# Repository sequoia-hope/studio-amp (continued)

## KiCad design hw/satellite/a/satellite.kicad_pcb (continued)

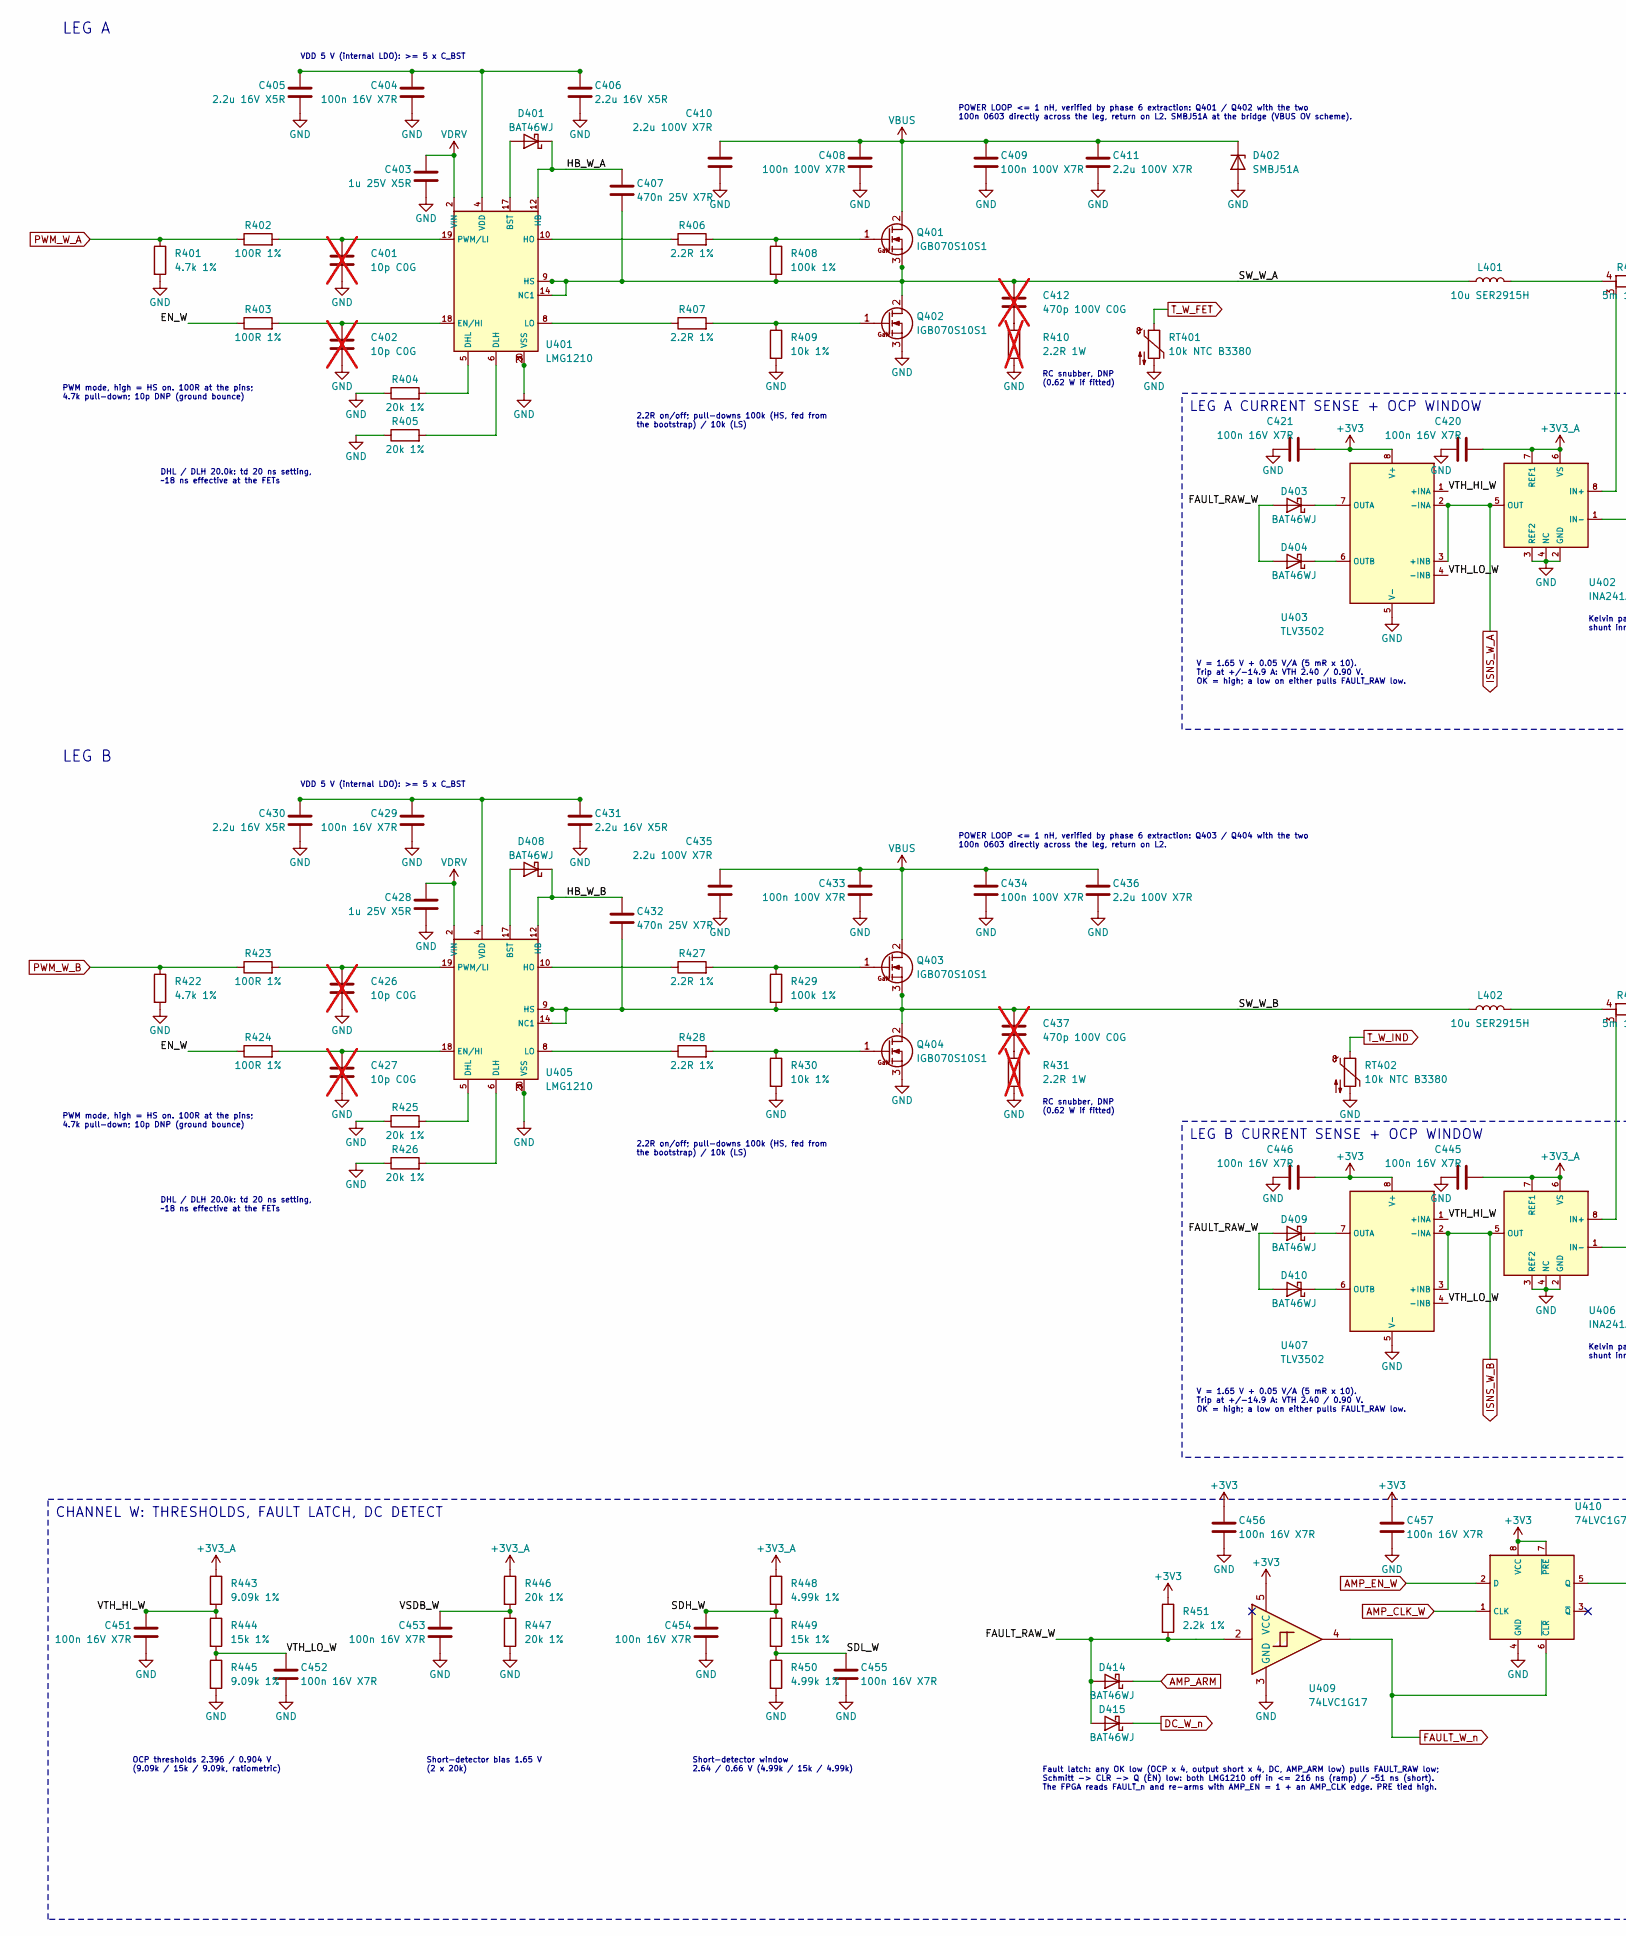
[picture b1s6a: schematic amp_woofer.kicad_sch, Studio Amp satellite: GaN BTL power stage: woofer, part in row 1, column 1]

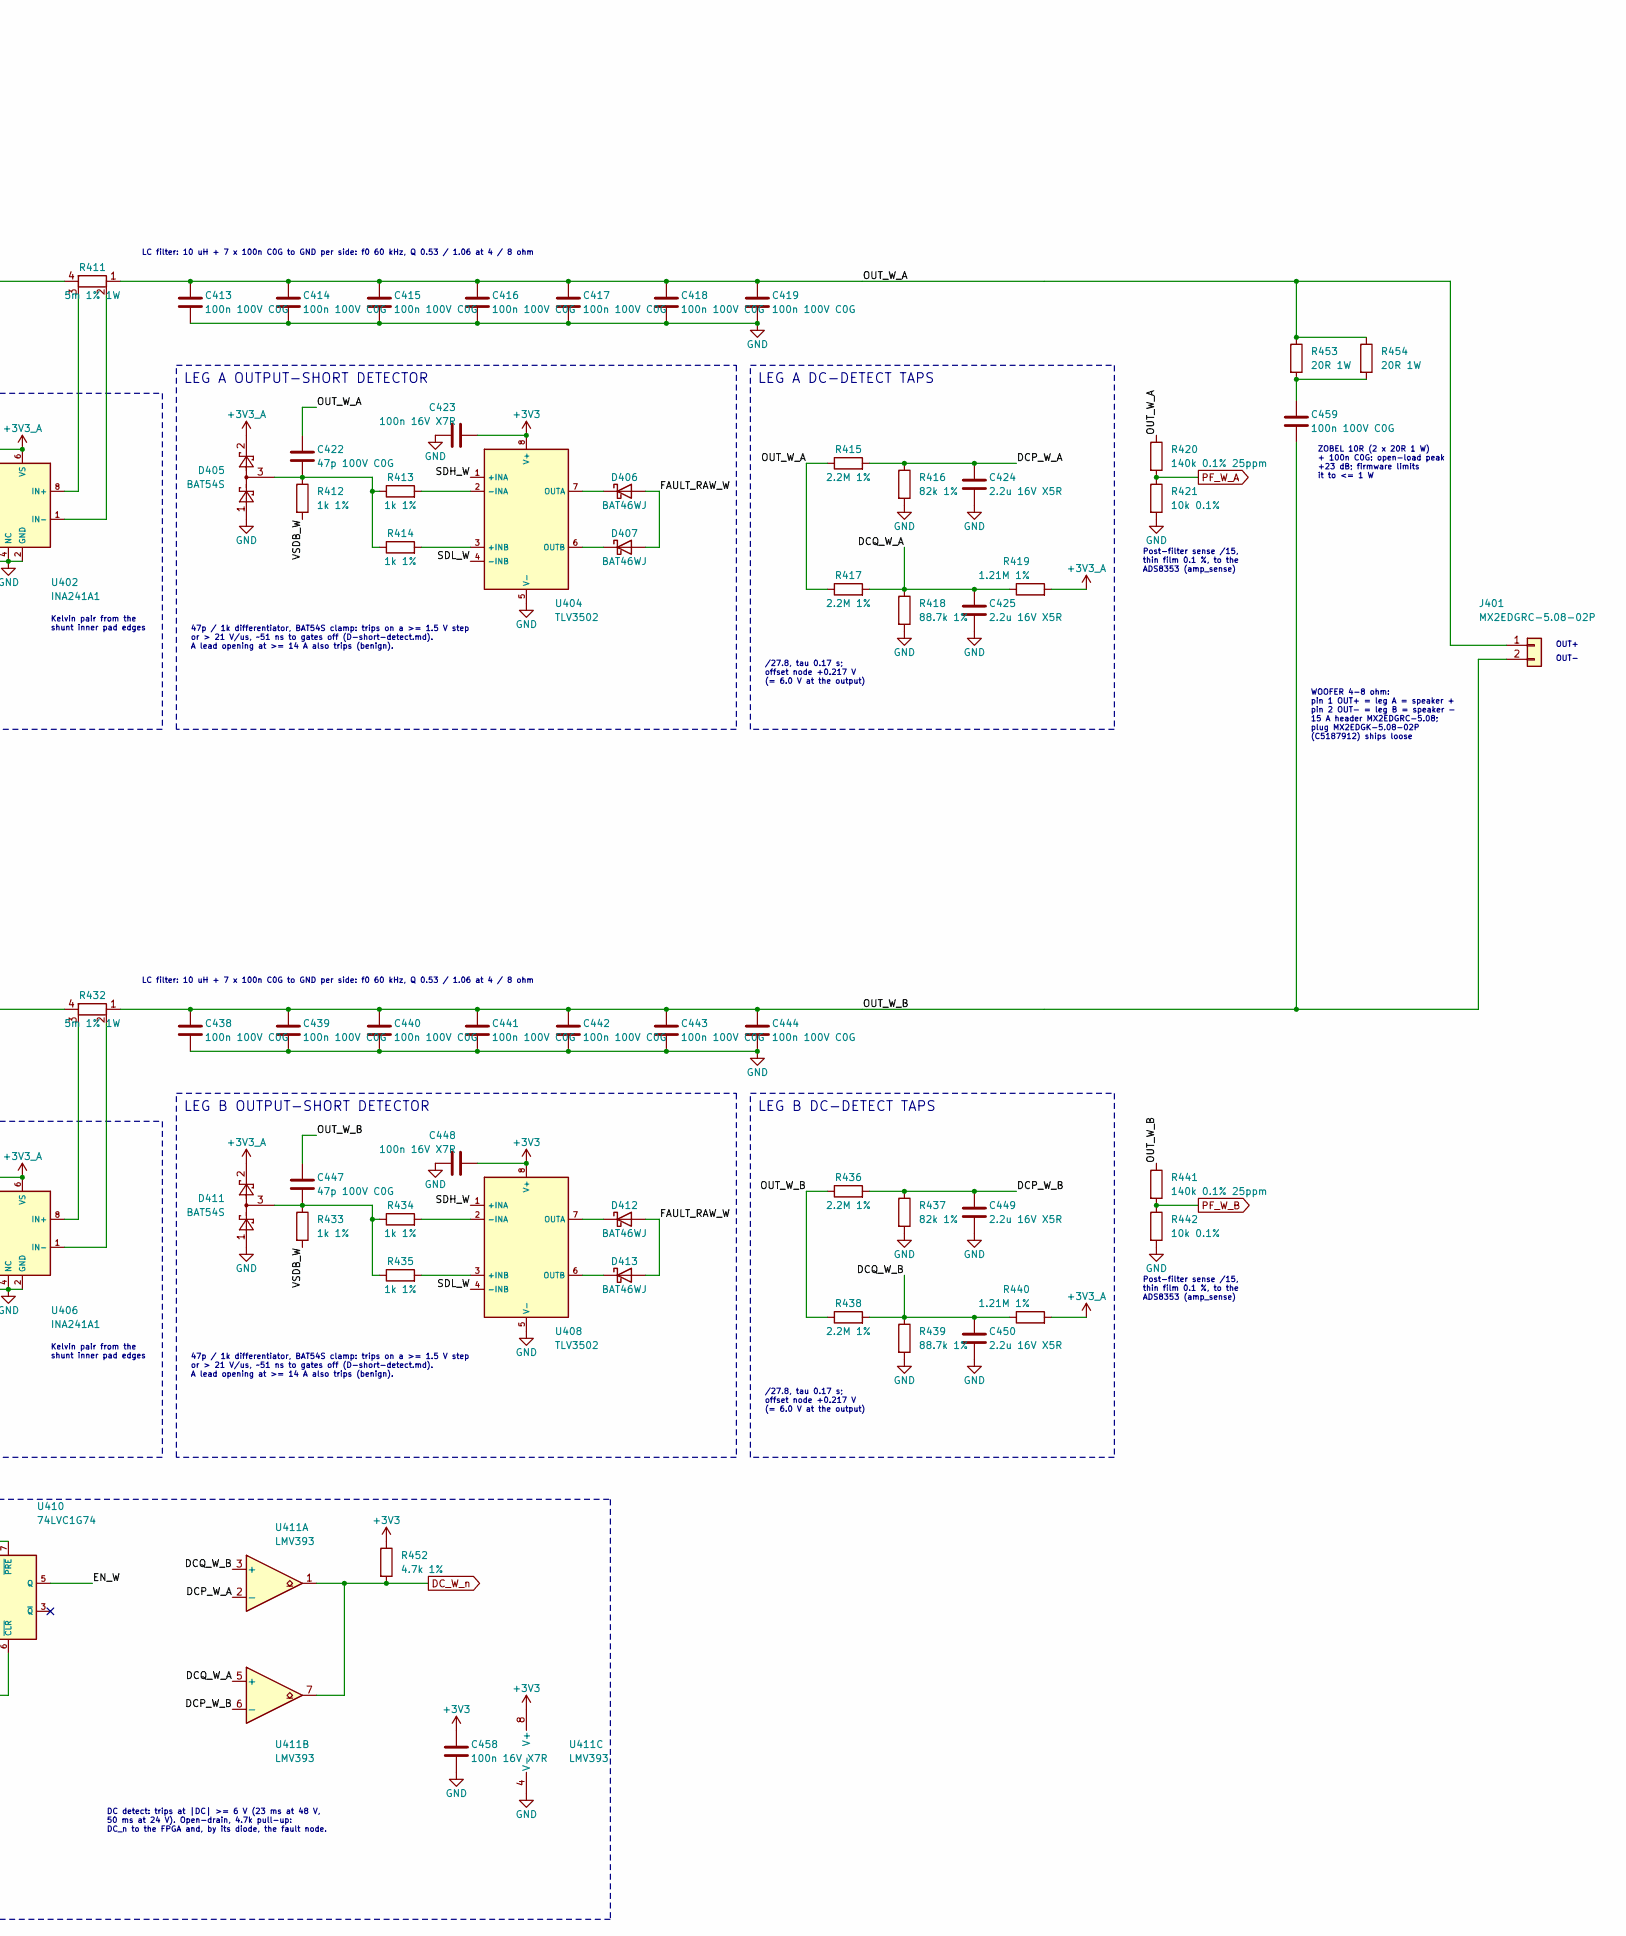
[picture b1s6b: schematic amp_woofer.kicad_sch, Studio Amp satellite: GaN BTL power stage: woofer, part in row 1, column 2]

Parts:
C401, C402, C426, C427: 10p C0G; C_0402_1005Metric; MPN 0402N100J500CT; LCSC C301961; not fitted
C403, C428: 1u 25V X5R; C_0603_1608Metric; MPN CL10A105KA8NNNC; LCSC C5673
C404, C420, C421, C423, C429, C445, C446, C448, C451, C452, C453, C454, C455, C456, C457, C458: 100n 16V X7R; C_0402_1005Metric; MPN CC0402KRX7R7BB104; LCSC C60474
C405, C406, C424, C425, C430, C431, C449, C450: 2.2u 16V X5R; C_0603_1608Metric; MPN CL10A225KO8NNNC; LCSC C23630
C407, C432: 470n 25V X7R; C_0603_1608Metric; MPN CL10B474KA8NNNC; LCSC C1623
C408, C409, C433, C434: 100n 100V X7R; C_0603_1608Metric; MPN HMK107B7104KAHT; LCSC C268011
C410, C411, C435, C436: 2.2u 100V X7R; C_1210_3225Metric; MPN HMK325B7225KN-T; LCSC C92775
C412, C437: 470p 100V C0G; C_0603_1608Metric; MPN CC0603JRNPO0BN471; LCSC C326973; not fitted
C413, C414, C415, C416, C417, C418, C419, C438, C439, C440, C441, C442, C443, C444, C459: 100n 100V C0G; C_1206_3216Metric; MPN GRM31C5C2A104JA01L; LCSC C405303
C422, C447: 47p 100V C0G; C_0603_1608Metric; MPN CC0603JRNPO0BN470; LCSC C327115
D401, D403, D404, D406, D407, D408, D409, D410, D412, D413, D414, D415: BAT46WJ; D_SOD-323F; MPN BAT46WJ,115; LCSC C114696
D402: SMBJ51A; D_SMB; MPN SMBJ51A; LCSC C1973217
D405, D411: BAT54S; SOT-23; MPN BAT54S,215; LCSC C47546
J401: MX2EDGRC-5.08-02P; MAX_MX2EDGRC-5.08-02P_1x02_P5.08mm_Horizontal; MPN MX2EDGRC-5.08-02P-GN01-Cu-A; LCSC C5188019
L401, L402: 10u SER2915H; Coilcraft_SER2915H; MPN SER2915H-103KL; LCSC C19276042
Q401, Q402, Q403, Q404: IGB070S10S1; IGB070S10S1_PG-TSON-4; MPN IGB070S10S1XTMA1; LCSC C44179579
R401, R422, R452: 4.7k 1%; R_0402_1005Metric; MPN 0402WGF4701TCE; LCSC C25900
R402, R403, R423, R424: 100R 1%; R_0402_1005Metric; MPN RC0402FR-07100RL; LCSC C106232
R404, R405, R425, R426, R446, R447: 20k 1%; R_0402_1005Metric; MPN 0402WGF2002TCE; LCSC C25765
R406, R407, R427, R428: 2.2R 1%; R_0402_1005Metric; MPN FRC0402F2R20TS; LCSC C2909330
R408, R429: 100k 1%; R_0402_1005Metric; MPN 0402WGF1003TCE; LCSC C25741
R409, R430: 10k 1%; R_0402_1005Metric; MPN 0402WGF1002TCE; LCSC C25744
R410, R431: 2.2R 1W; R_2512_6332Metric; MPN 25121WJ022JT4E; LCSC C25480; not fitted
R411, R432: 5m 1% 1W; R_2512_6332Metric_Kelvin_NetTie; MPN PA2512FKF070R005E; LCSC C723365
R412, R413, R414, R433, R434, R435: 1k 1%; R_0402_1005Metric; MPN 0402WGF1001TCE; LCSC C11702
R415, R417, R436, R438: 2.2M 1%; R_0603_1608Metric; MPN 0603WAF2204T5E; LCSC C22938
R416, R437: 82k 1%; R_0603_1608Metric; MPN 0603WAF8202T5E; LCSC C23254
R418, R439: 88.7k 1%; R_0603_1608Metric; MPN 0603WAF8872T5E; LCSC C23258
R419, R440: 1.21M 1%; R_0603_1608Metric; MPN 0603WAF1214T5E; LCSC C422998
R420, R441: 140k 0.1% 25ppm; R_0603_1608Metric; MPN RT0603BRD07140KL; LCSC C861125
R421, R442: 10k 0.1%; R_0603_1608Metric; MPN RT0603BRD0710KL; LCSC C95204
R443, R445: 9.09k 1%; R_0402_1005Metric; MPN 0402WGF9091TCE; LCSC C11549
R444, R449: 15k 1%; R_0402_1005Metric; MPN 0402WGF1502TCE; LCSC C25756
R448, R450: 4.99k 1%; R_0402_1005Metric; MPN 0402WGF4991TCE; LCSC C25903
R451: 2.2k 1%; R_0402_1005Metric; MPN 0402WGF2201TCE; LCSC C25879
R453, R454: 20R 1W; R_2512_6332Metric; MPN 25121WF200JT4E; LCSC C41950
RT401, RT402: 10k NTC B3380; R_0402_1005Metric; MPN NCP15XH103F03RC; LCSC C77131
U401, U405: LMG1210; Texas_RVR0019A_WQFN-19-2EP_4x3mm_P0.5mm; MPN LMG1210RVRR; LCSC C2677136
U402, U406: INA241A1; SOT-23-8; MPN INA241A1IDDFR; LCSC C19712054
U403, U404, U407, U408: TLV3502; SOT-23-8; MPN TLV3502AIDCNR; LCSC C48618
U409: 74LVC1G17; SOT-23-5; MPN SN74LVC1G17DBVR; LCSC C7836
U410: 74LVC1G74; VSSOP-8_2.3x2mm_P0.5mm; MPN SN74LVC1G74DCUR; LCSC C70285
U411: LMV393; SOIC-8_3.9x4.9mm_P1.27mm; MPN LMV393IDR; LCSC C7984

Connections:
+3V3_A: C420.2, C445.2, D405.2 (K), D411.2 (K), R419.2, R440.2, R443.1, R446.1, R448.1, U402.6 (VS), U402.7 (REF1), U406.6 (VS), U406.7 (REF1); also elsewhere on the board
/amp_woofer/DCP_W_A: C424.1, R415.2, R416.1, U411.2 (-)
/amp_woofer/DCP_W_B: C449.1, R436.2, R437.1, U411.6 (-)
/amp_woofer/DCQ_W_A: C425.1, R417.2, R418.1, R419.1, U411.5 (+)
/amp_woofer/DCQ_W_B: C450.1, R438.2, R439.1, R440.1, U411.3 (+)
/amp_woofer/EN_W: R403.1, R424.1, U410.5 (Q)
/amp_woofer/FAULT_RAW_W: D403.2 (A), D404.2 (A), D406.2 (A), D407.2 (A), D409.2 (A), D410.2 (A), D412.2 (A), D413.2 (A), D414.2 (A), D415.2 (A), R451.2, U409.2
/amp_woofer/HB_W_A: C407.1, D401.1 (K), U401.12 (HB)
/amp_woofer/HB_W_B: C432.1, D408.1 (K), U405.12 (HB)
/amp_woofer/OUT_W_A: C413.1, C414.1, C415.1, C416.1, C417.1, C418.1, C419.1, C422.1, J401.1, R411.1, R415.1, R417.1, R420.1, R453.1, R454.1
/amp_woofer/OUT_W_B: C438.1, C439.1, C440.1, C441.1, C442.1, C443.1, C444.1, C447.1, C459.2, J401.2, R432.1, R436.1, R438.1, R441.1
/amp_woofer/SDH_W: C454.1, R448.2, R449.1, U404.1 (+INA), U408.1 (+INA)
/amp_woofer/SDL_W: C455.1, R449.2, R450.1, U404.4 (-INB), U408.4 (-INB)
/amp_woofer/SW_W_A: C407.2, C412.1, L401.1, Q401.3 (S), Q401.4 (S), Q402.2 (D), R408.2, U401.9 (HS), U401.13 (HS), U401.14 (NC1), U401.16 (HS), U401.21 (HS)
/amp_woofer/SW_W_B: C432.2, C437.1, L402.1, Q403.3 (S), Q403.4 (S), Q404.2 (D), R429.2, U405.9 (HS), U405.13 (HS), U405.14 (NC1), U405.16 (HS), U405.21 (HS)
/amp_woofer/VSDB_W: C453.1, R412.2, R433.2, R446.2, R447.1
/amp_woofer/VTH_HI_W: C451.1, R443.2, R444.1, U403.1 (+INA), U407.1 (+INA)
/amp_woofer/VTH_LO_W: C452.1, R444.2, R445.1, U403.4 (-INB), U407.4 (-INB)
AMP_ARM: D414.1 (K); also elsewhere on the board
AMP_CLK_W: U410.1 (CLK); also elsewhere on the board
AMP_EN_W: U410.2 (D); also elsewhere on the board
DC_W_n: D415.1 (K), R452.2, U411.1, U411.7; also elsewhere on the board
FAULT_W_n: U409.4, U410.6 (~CLR); also elsewhere on the board
ISNS_W_A: U402.5 (OUT), U403.2 (-INA), U403.3 (+INB); also elsewhere on the board
ISNS_W_B: U406.5 (OUT), U407.2 (-INA), U407.3 (+INB); also elsewhere on the board
unnamed: C412.2, R410.1
unnamed: C437.2, R431.1
unnamed: C459.1, R453.2, R454.2
unnamed: D401.2 (A), U401.17 (BST)
unnamed: D403.1 (K), U403.7 (OUTA)
unnamed: D404.1 (K), U403.6 (OUTB)
unnamed: C422.2, D405.3 (COM), R412.1, R413.1, R414.1
unnamed: D406.1 (K), U404.7 (OUTA)
unnamed: D407.1 (K), U404.6 (OUTB)
unnamed: D408.2 (A), U405.17 (BST)
unnamed: D409.1 (K), U407.7 (OUTA)
unnamed: D410.1 (K), U407.6 (OUTB)
unnamed: C447.2, D411.3 (COM), R433.1, R434.1, R435.1
unnamed: D412.1 (K), U408.7 (OUTA)
unnamed: D413.1 (K), U408.6 (OUTB)
unnamed: L401.2, R411.4
unnamed: L402.2, R432.4
unnamed: Q401.1 (G), R406.2, R408.1
unnamed: Q402.1 (G), R407.2, R409.1
unnamed: Q403.1 (G), R427.2, R429.1
unnamed: Q404.1 (G), R428.2, R430.1
unnamed: R404.2, U401.5 (DHL)
unnamed: R405.2, U401.6 (DLH)
unnamed: C402.1, R403.2, U401.18 (EN/HI)
unnamed: R406.1, U401.10 (HO)
unnamed: R407.1, U401.8 (LO)
unnamed: C401.1, R402.2, U401.19 (PWM/LI)
unnamed: C404.1, C405.1, C406.1, U401.4 (VDD)
unnamed: R411.3, U402.8 (IN+)
unnamed: R411.2, U402.1 (IN-)
unnamed: R414.2, U404.3 (+INB)
unnamed: R413.2, U404.2 (-INA)
unnamed: R425.2, U405.5 (DHL)
unnamed: R426.2, U405.6 (DLH)
unnamed: C427.1, R424.2, U405.18 (EN/HI)
unnamed: R427.1, U405.10 (HO)
unnamed: R428.1, U405.8 (LO)
unnamed: C426.1, R423.2, U405.19 (PWM/LI)
unnamed: C429.1, C430.1, C431.1, U405.4 (VDD)
unnamed: R432.3, U406.8 (IN+)
unnamed: R432.2, U406.1 (IN-)
unnamed: R435.2, U408.3 (+INB)
unnamed: R434.2, U408.2 (-INA)
PF_W_A: R420.2, R421.1; also elsewhere on the board
PF_W_B: R441.2, R442.1; also elsewhere on the board
PWM_W_A: R401.1, R402.1; also elsewhere on the board
PWM_W_B: R422.1, R423.1; also elsewhere on the board
T_W_FET: RT401.1; also elsewhere on the board
T_W_IND: RT402.1; also elsewhere on the board

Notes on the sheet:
LEG A
PWM mode, high = HS on. 100R at the pins; 4.7k pull-down; 10p DNP (ground bounce)
DHL / DLH 20.0k: td 20 ns setting, ~18 ns effective at the FETs
VDD 5 V (internal LDO): >= 5 x C_BST
2.2R on/off; pull-downs 100k (HS, fed from the bootstrap) / 10k (LS)
POWER LOOP <= 1 nH, verified by phase 6 extraction: Q401 / Q402 with the two 100n 0603 directly across the leg, return on L2. SMBJ51A at the bridge (VBUS OV scheme).
RC snubber, DNP (0.62 W if fitted)
LC filter: 10 uH + 7 x 100n C0G to GND per side: f0 60 kHz, Q 0.53 / 1.06 at 4 / 8 ohm
Kelvin pair from the shunt inner pad edges
LEG A CURRENT SENSE + OCP WINDOW
V = 1.65 V + 0.05 V/A (5 mR x 10). Trip at +/-14.9 A: VTH 2.40 / 0.90 V. OK = high; a low on either pulls FAULT_RAW low.
LEG A OUTPUT-SHORT DETECTOR
47p / 1k differentiator, BAT54S clamp: trips on a >= 1.5 V step or > 21 V/us, ~51 ns to gates off (D-short-detect.md). A lead opening at >= 14 A also trips (benign).
LEG A DC-DETECT TAPS
/27.8, tau 0.17 s; offset node +0.217 V (= 6.0 V at the output)
Post-filter sense /15, thin film 0.1 %, to the ADS8353 (amp_sense)
LEG B
POWER LOOP <= 1 nH, verified by phase 6 extraction: Q403 / Q404 with the two 100n 0603 directly across the leg, return on L2.
LEG B CURRENT SENSE + OCP WINDOW
LEG B OUTPUT-SHORT DETECTOR
LEG B DC-DETECT TAPS
CHANNEL W: THRESHOLDS, FAULT LATCH, DC DETECT
OCP thresholds 2.396 / 0.904 V (9.09k / 15k / 9.09k, ratiometric)
Short-detector bias 1.65 V (2 x 20k)
Short-detector window 2.64 / 0.66 V (4.99k / 15k / 4.99k)
Fault latch: any OK low (OCP x 4, output short x 4, DC, AMP_ARM low) pulls FAULT_RAW low; Schmitt -> CLR -> Q (EN) low: both LMG1210 off in <= 216 ns (ramp) / ~51 ns (short). The FPGA reads FAULT_n and re-arms with AMP_EN = 1 + an AMP_CLK edge. PRE tied high.
DC detect: trips at |DC| >= 6 V (23 ms at 48 V, 50 ms at 24 V). Open-drain, 4.7k pull-up: DC_n to the FPGA and, by its diode, the fault node.
ZOBEL 10R (2 x 20R 1 W) + 100n C0G: open-load peak +23 dB; firmware limits it to <= 1 W
OUT+
OUT-
WOOFER 4-8 ohm: pin 1 OUT+ = leg A = speaker + pin 2 OUT- = leg B = speaker - 15 A header MX2EDGRC-5.08; plug MX2EDGK-5.08-02P (C5187912) ships loose

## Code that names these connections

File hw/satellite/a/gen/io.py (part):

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    # shell: 0R to GND fitted; 1M || 4n7 2 kV (DNP) is the isolated-shell option for EMC tests
    ysh = gp[1] + 10.16
    S.w(sh, (sh[0], ysh), (60.96, ysh))
    S.label("USB_SHIELD", (sh[0] + 2.54, ysh))
    vR_gnd("0R", (38.1, ysh), fields={"Note": "fit for shell to GND; remove to isolate"})
    vR_gnd("1M", (45.72, ysh), dnp=True, fields={"Note": "DNP: isolated-shell option"})
    S.C("4n7_2kV", (60.96, ysh + 3.81), dnp=True, fields={"Note": "DNP: isolated-shell option"})
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    vR_gnd("22k", (xd, y + 7.62))
    S.w((xd, y + 7.62), (132.08, y + 7.62))
    S.cap_down("100n", 124.46, y + 7.62)
    S.glabel("VUSB_DET", (132.08, y + 7.62), shape="output")


# ===================================================================== Qwiic
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    t = S.part("studio_G:TCA9617B", "U", "TCA9617B", (xt, y_sda), mirror="y",
               ref_at=(104.14, y_sda + 15.24), value_at=(104.14, y_sda + 17.018), justify="left")
    sclb, sdab, scla, sdaa, en = t.pin("7"), t.pin("6"), t.pin("2"), t.pin("3"), t.pin("5")
    # B side: straight to J pins 3/4 (no series R, G-qwiic.md), 2.2k pull-ups to QWIIC_PU
    S.w(p4, (p4[0], y_scl), (86.36, y_scl), (86.36, sclb[1]), sclb)
    S.w(p3, (p3[0], y_sda), sdab)
    S.label("QWIIC_SCL", (35.56, y_scl))
    S.label("QWIIC_SDA", (35.56, y_sda))
    pullup("2.2k", (66.04, y_scl), "QWIIC_PU")
    S.w((66.04, y_scl - 7.62), (50.8, y_scl - 7.62))
    S.flag((50.8, y_scl - 7.62))            # QWIIC_PU is fed through the jumper
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    S.cap_down("100n", 109.22, yb, dec=f"{t.ref}.1", vtext="right")
    # A side to the RP2350 I2C1; SCL lifts to its own lane so both 4.7k pull-ups hang clear
    S.w(scla, (116.84, scla[1]), (116.84, y_scl - 5.08), (129.54, y_scl - 5.08))
    S.glabel("I2C1_SCL", (129.54, y_scl - 5.08), shape="bidirectional")
    pullup("4.7k", (121.92, y_scl - 5.08), "+3V3")
    S.w(sdaa, (129.54, sdaa[1]))
    S.glabel("I2C1_SDA", (129.54, sdaa[1]), shape="bidirectional")
    pullup("4.7k", (124.46, sdaa[1]), "+3V3")
    S.text("A-side 4.7k: drop if block E\nfits I2C1 pull-ups", (106.68, 22.86))
    # EN: QWIIC_PWR_EN, 10k pull-down (beats the -25 uA internal pull-up)
    S.w(en, (129.54, en[1]))
    S.glabel("QWIIC_PWR_EN", (129.54, en[1]), shape="input")
    vR_gnd("10k", (124.46, en[1]), vtext="left")
    # power: +3V3 -> TPS2553 (RILIM 150k) -> QWIIC_3V3 -> J pin 2
    sw, P = switch("TPS2553", (76.2, 91.44), ref_at=(50.8, 80.01), value_at=(50.8, 81.788), justify="left")
    S.rail("+3V3", (50.8, P["IN"][1]))
    S.w((50.8, P["IN"][1]), P["IN"])
    S.cap_down("1u_50V_0603", 58.42, P["IN"][1], dec=f"{sw.ref}.1")
    S.w(P["EN"], (63.5, P["EN"][1]), (63.5, 106.68), (55.88, 106.68))
    S.glabel("QWIIC_PWR_EN", (55.88, 106.68), rot=180, shape="input")
    S.gnd(P["GND"])
    vR_gnd("150k", P["ILIM"], vtext="right")
    xo = P["OUT"][0] + 5.08
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    # FAULT -> QWIIC_FAULT_N, 10k to +3V3
    S.w(P["FLT"], (P["FLT"][0] + 2.54, P["FLT"][1]), (P["FLT"][0] + 2.54, 106.68), (129.54, 106.68))
    pullup("10k", (114.3, 106.68), "+3V3")
    S.glabel("QWIIC_FAULT_N", (129.54, 106.68), shape="output")
    # ESD on SDA/SCL: SRV05-4 (3 pF), rail QWIIC_3V3
    srv05((33.02, 124.46), (None, None), ("QWIIC_SCL", "QWIIC_SDA"), rail="QWIIC_3V3")
    S.text("No series R on SDA/SCL: a far-end low\nplus I*R must stay below VILB 0.4 V", (63.5, 124.46))
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    S.w((17.78, y), P["IN"])
    S.cap_down("1u_50V_0603", 22.86, y, dec=f"{sw.ref}.6", vtext="left")
    S.w(P["EN"], (27.94, P["EN"][1]), (27.94, 58.42), (22.86, 58.42))
    S.glabel("LED_EN", (22.86, 58.42), rot=180, shape="input")
    vR_gnd("100k", (27.94, 58.42), vtext="right")
    S.gnd(P["GND"])
    vR_gnd("23.2k", P["ILIM"], vtext="right")
    S.w(P["FLT"], (53.34, P["FLT"][1]), (53.34, 58.42), (66.04, 58.42))
    pullup("10k", (58.42, 58.42), "+3V3", vtext="right")
    S.glabel("LED_FAULT_N", (66.04, 58.42), shape="output")
    S.text("RILIM 23.2k: 1.03-1.20 A;\nfirmware caps it by PoE class", (50.8, 22.86))
    # +5V_LED -> 22u -> BLM31KN601 -> SMF6.0A -> J pin 1 (J at the top right, pins down)
    j = S.part("studio_G:Conn_LED_PH4", "J", "JST_PH4", (132.08, 38.1),
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    tvs("SMF6.0A", (114.3, y), left=True)
    S.gnd(c2)
    # level shifters on +5V_LED (OE tied low), 47R + PESD to J pins 3 (D) and 4 (C)
    for pin, name, uy, xv in ((c3, "LED_DATA", 81.28, 119.38), (c4, "LED_CLK", 116.84, 121.92)):
        u = S.part("74xGxx:74LVC1G125", "U", "SN74LV1T125", (66.04, uy),
                   ref_at=(68.58, uy + 7.62), value_at=(68.58, uy + 9.398), justify="left",
                   footprint="Package_TO_SOT_SMD:SOT-23-5")
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        else:
            S.w(p, (xv, p[1]), (xv, ly), (xr, ly))
        if name == "KNOB_REF":
            S.label("KNOB_REF", (55.88, ly))
            S.cap_down("1u_50V_0603", 66.04, ly, vtext="right")
            hR("100R", (xr, ly))
            S.w((xr + 7.62, ly), (86.36, ly))
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        hR("47R", (233.68, Y))
        S.w((241.3, Y), (254.0, Y))
        S.glabel(fpga[k], (254.0, Y), shape="input")
    S.text("Each position: a jumper to DISP_VCC, DISP_BL_SW (switched backlight) or GND, else 47R to its FPGA pin.\n"
           "Defaults for GND, VCC, SCL, SDA, RES, DC, CS, BLK: JP to GND on 1, VCC on 2, BLK on 8\n"
           "bridged. An FPGA line whose position is jumpered must be constrained Hi-Z (block E).",
           (137.16, 22.86))
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
def backlight():
    """DISP_VCC ferrite and the backlight high-side switch (AO3401A + 2N7002). Its output rail is
    DISP_BL_SW: DISP_BLK is already the FPGA line to header position 8 (E-pinmap.md)."""
    S.box((12.7, 15.24), (284.48, 66.04), "DISP_VCC AND BACKLIGHT SWITCH  (G-display.md)")
    y = 30.48
    S.rail("+3V3", (17.78, y))
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    hR("100R", (ng[0] - 10.16, ng[1]))
    vR_gnd("100k", (ng[0] - 2.54, ng[1]), vtext="right")
    S.w((ng[0] - 10.16, ng[1]), (ng[0] - 17.78, ng[1]))
    S.glabel("DISP_BL_PWM", (ng[0] - 17.78, ng[1]), rot=180, shape="input")
    S.text("PWM <= 2 kHz with the 100k gate pull-up\n(10k for faster PWM). Q off at power-up.", (165.1, 40.64))


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
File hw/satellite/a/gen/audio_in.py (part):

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W(r_bias.pin("2"), (x_rb, y_nb))
W((x_cnb, y_nb), c_nb.pin("1"))
J((x_rb, y_nb)); J((x_cnb, y_nb))
sch.label("MIC_BIAS", (111.76, y_nb))
T("Plug-in power: 5.0 V open circuit through 4.4 kΩ,\n2.8-3.7 V at a 0.3-0.5 mA electret\n(R-15 deviation, F-overview.md).\nR_F with 47 µF: 1.5 Hz filter on +5V_A.",
  (25.4, 140.97))
# tip line
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W(tip, (x_tt, Y), (x_rb, Y), c_in.pin("1"))
W((x_tt, Y), d_t.pin("1")); W((x_rb, Y), r_bias.pin("1"))
J((x_tt, Y)); J((x_rb, Y))
sch.label("MIC_TIP", (43.18, Y))

# =====================================================================================
# 2. PREAMP: SA5532 half A, +12 dB (F-mic-adc-pcm1808.md, F-opamp-sa5532.md)
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W(r_s.pin("2"), (x_cl, Y), (x_b, Y), ua.pin("3"))
W((x_b, Y), r_b.pin("1"))
J((x_cl, Y)); J((x_b, Y))
sch.label("MIC_PRE_IN", (182.88, Y))
# feedback: Rg to ground, Rf || Cf from out to -IN
nin, out = ua.pin("2"), ua.pin("1")
x_g, yfb = 190.5, Y + 17.78
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x_c2 = 259.08
c_adc = hC("1u_film", x_c2, Y, note="PET film coupling (review M2); 2.65 Hz with 60 kΩ")
W((x_o, out[1]), (233.68, out[1]), (233.68, Y), c_adc.pin("1"))
sch.label("MIC_PRE", (236.22, Y))
r_a = hR("2k2", 274.32, Y, note="R_A: limits clamp current to 5.7 mA")
W(c_adc.pin("2"), r_a.pin("1"))
x_j = 287.02                                          # clamp junction, BAT54S hangs below
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W(r_bb.pin("2"), (x_cp, Y), u.pin("13"))
W((x_cp, Y), c_pin.pin("1")); J((x_cp, Y))
pl.gnd(c_pin.pin("2"))
sch.label("ADC_VINL", (318.77, Y))
# supplies: VCC (+5V_A) and VDD (+3V3), each 100 nF + 10 uF at the pin
vcc, vdd = u.pin("3"), u.pin("4")
y_vcc, y_vdd = 50.8, 43.18
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c_r2 = vC("10u_al", 365.76, y_b + 5.08, polar=True, decouples=f"{u.ref}.1")
W((350.52, y_b), c_r1.pin("1")); W((365.76, y_b), c_r2.pin("1")); J((350.52, y_b))
pl.gnd(c_r1.pin("2")); pl.gnd(c_r2.pin("2"))
sch.label("ADC_VREF", (340.36, y_b))
y_g = vref[1] + 5.08
gp = [u.pin(n) for n in ("2", "5", "10", "11", "12")]
for p in gp:
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    J((p[0], y_g))
W((gp[2][0], y_g), (gp[2][0], y_g + 2.54)); pl.gnd((gp[2][0], y_g + 2.54))
T("MD1 = MD0 = L: slave, SCKI auto-detect\nFMT = L: I2S 24-bit", (312.42, 137.16))
# FPGA side: SCKI from the MCLK_Q buffer (audio_out), I2S to the ECP5 (E-pinmap.md)
x_lab = 381.0
for pin, name, shape in (("6", "MCLK_ADC", "input"), ("8", "MADC_BCK", "input"),
                         ("7", "MADC_LRCK", "input"), ("9", "MADC_DOUT", "output")):
    p = u.pin(pin)
    W(p, (x_lab, p[1]))
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# =====================================================================================
sch.box((139.7, 160.02), (325.12, 254.0), "LOOPBACK: LINE-OUT L (FILT_L) -> PCM1808 VINR (OPTIONAL, R_LA AND C_LB DNP)")
YL = 195.58
glabel("FILT_L", (147.32, YL), rot=180, shape="input")
r_la = pl.R("10k", (158.75, YL), horiz=True, ref_at=(155.0, YL - 6.35), value_at=(155.0, YL + 6.35), dnp=True, note="DNP: fit for latency/level loopback")
W((147.32, YL), r_la.pin("1"))
x_d = 172.72
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W(r_b2.pin("2"), (x_cp2, o2[1]), (x_v, o2[1]), (x_v, vinr[1]), vinr)
W((x_cp2, o2[1]), c_pin2.pin("1")); J((x_cp2, o2[1]))
pl.gnd(c_pin2.pin("2"))
sch.label("ADC_VINR", (284.48, o2[1]))
T("Not fitted: R_LA and C_LB. With them, VINR records line-out L\nfor latency and level calibration (room correction).", (144.78, 241.3))

# =====================================================================================
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sch.box((330.2, 160.02), (403.86, 254.0), "ON-BOARD MEMS MIC (R-16)")
mk = pl.part("studio_F:T3902", "MK", "T3902", (370.84, 210.82), ref_at=(381.0, 217.17), value_at=(381.0, 219.71))
clk, sel, dat, vdd2, gnd2 = mk.pin("4"), mk.pin("2"), mk.pin("1"), mk.pin("5"), mk.pin("3")
glabel("PDM_CLK", (335.28, clk[1]), rot=180, shape="input")
r_pc = hR("33R", 345.44, clk[1], top=True, note="PDM_CLK source series: place at ECP5 ball L14 (F-mems-t3902.md)")
W((335.28, clk[1]), r_pc.pin("1")); W(r_pc.pin("2"), clk)
W(sel, (355.6, sel[1]), (355.6, sel[1] + 7.62)); pl.gnd((355.6, sel[1] + 7.62))
T("SELECT = GND: data on the right\nchannel (after CLK falls)", (335.28, 236.22))
W(dat, (391.16, dat[1])); glabel("PDM_DAT", (391.16, dat[1]), rot=0, shape="output")
pl.gnd(gnd2)
y_mv = vdd2[1] - 7.62
r_mv = hR("10R", 383.54, y_mv)
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
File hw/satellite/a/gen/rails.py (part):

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    S.w((104.14, bst[1] - 7.62), (109.22, bst[1] - 7.62), (109.22, sw[1]))
    # switch node, catch diode, inductor
    S.w(sw, (139.7, sw[1]))
    S.label("SW_5V", (124.46, sw[1]))
    d = S.part("studio_C:D_Schottky_TO277A", "D", "SS5P10", (134.62, sw[1] + 5.08), rot=90,
               ref_at=(138.43, sw[1] + 4.064), value_at=(138.43, sw[1] + 5.842))
    S.gnd(d.pin("1"))
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    S.flag((177.8, yo))
    S.text("+5V_BUCK 5.04 V: 0.91 A design\n1.75 A with the LED port at its limit", (147.32, 27.94))
    # PGOOD -> PG_5V (divider 56k/100k at the TPS2116, C-5v-buck.md)
    S.label("PG_5V", pg)
    # feedback divider at FB (0.5 %): 100k / 31.6k -> 5.04 V with the Type 3 offset
    fx = 109.22
    S.w(fb, (fx, fb[1]), (fx, 68.58))
    S.label("FB_5V", (fx, 60.96))
    vR_gnd("31.6k_0.5", (fx, 68.58), vtext="left")
    hR("100k_0.5", (fx, 68.58))
    S.w((fx + 7.62, 68.58), (fx + 15.24, 68.58))
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    # Type 3 ripple network (RA from SW, CA to VOUT, CB to FB), drawn beside the output caps;
    # in layout it sits at FB like the divider
    xn, yt = 165.1, 66.04
    S.label("SW_5V", (xn, yt))
    S.R("330k_0805", (xn, yt + 3.81), ref_at=(xn - 2.54, yt + 2.54), value_at=(xn - 2.54, yt + 4.318),
        justify="right", vtext=False)
    xy = yt + 7.62
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    S.C("330p", (xn, xy + 3.81), ref_at=(xn - 2.54, xy + 3.302), value_at=(xn - 2.54, xy + 5.08),
        justify="right", vtext=False)
    S.w((xn, xy + 7.62), (xn, xy + 10.16), (xn - 7.62, xy + 10.16))
    S.label("FB_5V", (xn - 7.62, xy + 10.16), rot=180)
    S.text("Hot loop C301-U301-D301 tight.\nFB parts at pin 5, away from SW.\nSW_5V: pad + GND spring site (io)",
           (15.24, 76.2))
    S.text("UVLO on 30.2 V / off 28.2 V", (38.1, 50.8))
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    S.w((208.28, 45.72), (208.28, 49.53))
    S.w((208.28, 57.15), (208.28, pr1[1]), pr1)
    vR_gnd("100k", (208.28, pr1[1]))
    S.label("PG_5V", (210.82, pr1[1]))
    # VIN2 from USB, 4u7 at the pin
    S.w(vin2, (vin2[0], 35.56))
    S.rail("VUSB", (vin2[0], 35.56))
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    S.w((256.54, 81.28), (261.62, 81.28))
    S.rail("+3V3", (261.62, 81.28))
    S.w((248.92, 81.28), (246.38, 81.28))
    S.label("PWR_FROM_POE", (246.38, 81.28), rot=180)


# ===================================================================== row 1: 3V3, 1V1
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    hR("100k", (px - 7.62, 78.74))
    S.w((px - 7.62, 78.74), (px - 12.7, 78.74))
    S.rail("+3V3", (px - 12.7, 78.74))
    S.label("PG_3V3", (px + 12.7, 78.74))
    S.text("3V3 = 0.6 x (1 + 100k/22.0k) = 3.33 V\n0.1 %: ECP5 VCCIO max 3.465 V\n"
           "+3V3: 0.79 A design (2 A part)", (276.86, 27.94))

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    S.flag((459.74, y))
    S.cap_down("10u_25V", 462.28, y, dec=f"{u.ref}.1")
    S.w(enuv, (474.98, enuv[1]))
    S.label("PG_3V3", (474.98, enuv[1]), rot=180)
    # NR/SS: R_NR 16.7k 0.1 % -> 2.505 V; C_NR 2.2 uF (above the 1 uF minimum) -> ~5 ms start
    S.w(nr, (477.52, nr[1]))
    vC("2u2_10V_0603", (477.52, nr[1]))
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def vdrv():
    y = 109.22
    S.box((12.7, 96.52), (200.66, 177.8), "GATE-DRIVE SUPPLY  VDRV 7.0 V  LM5017 + TLV6703  (C-vdrv-buck.md)")
    u, sw = lm5017(y, "VBUS -> VDRV", "191k_0805", "46.4k", "330k_0805", "VDRV", en_label="VDRV_EN",
                   sw_name="SW_VDRV")
    S.w(sw, (127.0, sw[1]))
    Lh("L47u_SRN6045", (130.81, sw[1]))
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    S.w((ox, yo + 7.62), (ox, out[1]))
    vR_gnd("2.7k", (ox, out[1]), vtext="right")
    S.w((ox, out[1]), (ox + 5.08, out[1]))
    S.glabel("VDRV_PG", (ox + 5.08, out[1]), shape="output")
    S.text("VDRV_EN low = off (100k pull-down).\nFirmware enables after FPGA DONE,\n"
           "PD_PG_N low and POE_LOSS_N high.\nVDRV 7.01-7.12 V typ (Type III offset)\n"
           "VDRV: 200 mA design (76 mA typ, block D)", (15.24, 160.02))
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    vR("100k", (383.54, 142.24))
    S.rail("+3V3", (383.54, 142.24))
    S.w((383.54, 149.86), (391.16, 149.86))
    S.glabel("PG_3V3Q", (391.16, 149.86), shape="output")
    S.text("SNS: Kelvin trace to the 74LVC74 row (block F)\nCOUT ceramic, ESR <= 20 mOhm\n"
           "+3V3_Q: 35 mA design", (276.86, 162.56))

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
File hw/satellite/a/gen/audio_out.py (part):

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        W(rs.pin("2"), d)
        glabel(f"DAC_{sfx}{k}", rs.pin("1"), rot=180, shape="input")
        W(c, (c[0] - 2.54, c[1]), (c[0] - 2.54, c[1] + 7.62))
        label("MCLK_FF", (c[0] - 2.54, c[1] + 7.62), rot=180)
        pl.pwr("+3V3_Q", s)
        W(r, (r[0], r[1] + 2.54), (r[0] + 5.08, r[1] + 2.54))
        pl.pwr("+3V3_Q", (r[0] + 5.08, r[1] + 2.54))
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    W((X_FB, pin_o[1]), (X_FB, y_c2), (X_FB, y_r3))
    J((X_FB, pin_o[1])); J((X_FB, y_c2))
    if ch == "L":      # FILT_L is also the loopback net to audio_in, so it is global everywhere
        glabel("FILT_L", (X_FB + 1.27, pin_o[1]), rot=90, shape="output")
    else:
        label(f"FILT_{sfx}", (X_FB + 1.27, pin_o[1]))
    # ---------------------------------------------------------------- DC servo (above the filter)
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b2 = pl.part("74xGxx:74LVC2G34", "U", "LVC2G34", (53.34, yb2), unit=2, ref=U_CK,
             ref_at=(48.26, yb2 + 5.08), value_at=(48.26, yb2 + 7.62))
ym_in = (yb1 + yb2) / 2
glabel("MCLK_Q", (25.4, ym_in), rot=180, shape="input")
W((25.4, ym_in), (33.02, ym_in))
W((33.02, yb1), (33.02, yb2))
W((33.02, yb1), b1.pin("1")); W((33.02, yb2), b2.pin("3")); J((33.02, ym_in))
r_ff = hR("22R", 73.66, yb1, top=True, note="1Y: the 8 flip-flop clock inputs")
W(b1.pin("6"), r_ff.pin("1"))
W(r_ff.pin("2"), (81.28, yb1)); label("MCLK_FF", (81.28, yb1))
r_ad = hR("33R", 73.66, yb2, top=True, note="2Y: PCM1808 SCKI (audio_in)")
W(b2.pin("4"), r_ad.pin("1"))
W(r_ad.pin("2"), (81.28, yb2)); glabel("MCLK_ADC", (81.28, yb2), rot=0, shape="output")
bp = pl.part("74xGxx:74LVC2G34", "U", "LVC2G34", (60.96, YM + 20.32), unit=3, ref=U_CK,
             ref_at=(63.5, YM + 19.05), value_at=(63.5, YM + 21.59))
pwr_above("+3V3_Q", bp.pin("5"), 2.54)
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x_bus0 = 381.0
W((x_bus0, Y_DC), (x1[0], Y_DC), (x2[0], Y_DC)); J((x1[0], Y_DC))
W((x_bus0, Y_PL), (x1[1], Y_PL), (x2[1], Y_PL)); J((x1[1], Y_PL))
glabel("HP_FAULT_N", (x_bus0, Y_DC), rot=180, shape="bidirectional")
glabel("POE_LOSS_N", (x_bus0, Y_PL), rot=180, shape="input")
T("/DC_TRIP (= HP_FAULT_N) or POE_LOSS_N low\npulls both gates to ≤ 0.37 V: relays open\nin hardware (F-mute-relay.md)",
  (515.62, 245.11))

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tvd = pl.part("Device:D_TVS", "D", "PESD15", (x_sn, y_hd + 3.81), rot=270, ref_at=(x_sn - 3.81, y_hd + 2.54), value_at=(x_sn - 3.81, y_hd + 5.08), justify="right")
W((x_sn, y_hd), tvd.pin("1")); gnd_below(tvd.pin("2")); J((x_sn, y_hd))
W((x_sn, y_hd), (x_sn + 5.08, y_hd))
glabel("HP_DET", (x_sn + 5.08, y_hd), rot=0, shape="output")

# ---- line-out RCA jacks
for i, (no, name, yj) in enumerate(((k2.pin("4"), "L", 170.18), (k2.pin("5"), "R", 226.06))):
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W((x_nd, yd[0]), (x_nd, 99.06))
for y in yd[1:]:
    J((x_nd, y))
label("N_DC", (x_nd, 81.28))
cdc = vC("10u_1206", 553.72, 90.17, note="non-polar X7R: tau 0.12 s with 4 x 47k")
W((x_nd, 86.36), (553.72, 86.36), cdc.pin("1")); J((x_nd, 86.36)); gnd_below(cdc.pin("2"))
rb1 = hR("10k", 551.18, 55.88, top=True)
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W(qdp.pin("3"), (562.61, 114.3), (x_tr, 114.3)); J((x_tr, 114.3))
rpu = vR("4k7", x_tr, 39.37, note="/DC_TRIP pull-up, read in hardware (re-review MINOR-3)")
W(rpu.pin("2"), (x_tr, 45.72)); J((x_tr, 45.72)); pwr_above("+3V3", rpu.pin("1"))
glabel("HP_FAULT_N", (x_tr, 119.38), rot=270, shape="output")
T("Trips at ±0.6 V on N_DC:\n2.4 V DC on one output,\n~30 ms incl. relay release.\nFILT_L is a global label: the\nsame net feeds the audio_in\nloopback. FILT_R is local.", (521.97, 127.0))

sch.save()
print("wrote", sch.file)
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
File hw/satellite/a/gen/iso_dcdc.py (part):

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    r214 = R("R214", "10k", (251.46, 139.7), tf="n", ref_at=(247.65, 141.0), value_at=(249.43, 141.0), ref_rot=90, justify="")
    w((251.46, gate[1]), r214.pin("1"))
    w(r214.pin("2"), r216.pin("1"))
    b.lab("CS_PRI", (256.54, r216.pin("1")[1]), 270)

    # =================================================================== UCC2897A
    u = b.part("studio_B:UCC2897A", "U201", "UCC2897A", (190.50, 139.7), tf="n",
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    w(c209.pin("1"), c210.pin("1"), (271.78, c210.pin("1")[1]), (271.78, 125.73), (xs, 125.73))
    sch.text("Active clamp, P-FET low side:\nVc ~ 100 V on C209 || C210 (250 V X7R).\nB-primary-power.md",
             (223.52, 203.2))
    # CS: RF 1k + CF 82p at the pin; Kelvin from the Rcs pad via CS_PRI
    cs = pin("9")
    c204 = C("C204", "82p", (226.06, 152.4), tf="v")
    r205 = R("R205", "1k", (233.68, 154.94), tf="v")
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    vin = pin("1")
    r218 = R("R218", "100k_8", (154.94, 119.38))
    w(vin, (154.94, vin[1]), r218.pin("2"))
    vcc(r218.pin("1"), "VPRI")
    r219 = R("R219", "0R", (142.24, 119.38), dnp=True, tf="l")
    w((154.94, vin[1]), (142.24, vin[1]), r219.pin("2"))
    vcc(r219.pin("1"), "VB_PRI")
    sch.text("VIN: 100k from VPRI (JFET start-up unused;\nVDD from VB_PRI). R219 DNP option.", (93.98, 99.06))
    luv = pin("18")
    r206 = R("R206", "73k2_8", (119.38, 127.0), tf="l")
    r207 = R("R207", "2k37", (119.38, 142.24), tf="l")
    w(luv, (119.38, luv[1]))
    w(r206.pin("2"), (119.38, luv[1]), r207.pin("1"))
    vcc(r206.pin("1"), "VPRI")
    rtn(r207.pin("2"))
    sch.text("LINEUV: on 40.4 V,\noff 38.4 V", (93.98, 152.4))
    b.glab("ACF_SYNC", pin("7"), 180, "input")
    b.lab("ACF_FB", pin("11"), 180)
    lov = pin("19")
    r210 = R("R210", "23k7", (154.94, 157.48), tf="v")
    c207 = C("C207", "47n", (144.78, 157.48), tf="vl")
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    # SS/SD: PD_PG holds it low through 1k during PD inrush; UCC_SS -> block A's PD_PG_N buffer
    w((ss[0], 165.1), (162.56, 165.1), (162.56, 173.99))
    r217 = R("R217", "1k", (162.56, 177.8), tf="l")
    b.glab("PD_PG", r217.pin("2"), 270, "input")
    w((162.56, 168.91), (149.86, 168.91))
    b.glab("UCC_SS", (149.86, 168.91), 180, "output")
    sch.box((88.90, 88.9), (276.86, 215.9), "UCC2897A CONTROLLER, PRIMARY STAGE")
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    b.lab("ACF_FB", (243.84, oc[1]), 180)
    r211 = R("R211", "4k99", (259.08, 264.16), tf="l")
    w(r211.pin("2"), (259.08, oc[1]))
    vcc(r211.pin("1"), "VREF_ACF")
    c206 = C("C206", "6n8", (251.46, 276.86), tf="l")
    w((251.46, oc[1]), c206.pin("1"))
    w(oe, (266.7, oe[1]), (266.7, 284.48))
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    w(oa, (292.1, oa[1]), (292.1, 266.7))
    r247 = R("R247", "499", (292.1, 261.62), tf="n", ref_at=(294.13, 263.5), value_at=(295.91, 263.5), ref_rot=90, justify="")
    w(r247.pin("2"), (292.1, 266.7))
    vcc(r247.pin("1"), "VSR")
    r248 = R("R248", "1k", (302.26, 269.24), tf="v")
    w((292.1, 266.7), (302.26, 266.7), r248.pin("1"))
    yk = ok[1]
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
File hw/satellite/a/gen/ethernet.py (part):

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sch.wire(far, (far[0] + 5.08, y1))
d.rail("+3V3", (far[0] + 5.08, y1))
# the magjack's PHY-side centre taps (J101 12, 6) and the yellow LED anode (18) are ETH_AVDD too:
# block A puts ETH_AVDD power symbols on those pins. Their two bypass caps go at J101.
xc = xr + 2.54
for i, pinj in enumerate(("12", "6")):
    x = xc + 7.62 + 12.7 * i
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r, a, b = d.series("33R", (node[0] + 10.16, node[1] + 10.16))
sch.wire((node[0], node[1] + 10.16), a)
sch.wire(b, (node[0] + 22.86, node[1] + 10.16))
d.glabel("RMII_REFCLK", (node[0] + 22.86, node[1] + 10.16), "R", "output")
T("RMII REFERENCE CLOCK: 50 MHz +-50 ppm CMOS XO, OE tied high.\nTwo point-to-point branches, 33R each at the XO:\n"
  "PHY XTAL1 and ECP5 C8 (PCLKT1_0), <= 25 mm,\nmatched +-5 mm, over solid GND.", (XO[0] - 7.62, XO[1] + 22.86))

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d.gnd(vc.pin("2"))
# tune: VCXO_TUNE (ECP5 N4, delta-sigma) -> 100k -> 1u -> 100k -> 1u -> 0R -> Vc  (2 poles at 1.59 Hz)
x0 = 35.56
d.glabel("VCXO_TUNE", (x0, VY), "L", "input")
r1, a1, b1 = d.series("100k", (x0 + 10.16, VY))
sch.wire((x0, VY), a1)
n1 = (x0 + 17.78, VY)
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sch.wire((vvdd[0] + 30.48, yr), lo)
sch.wire(hi, (hi[0] + 5.08, yr))
d.rail("+3V3", (hi[0] + 5.08, yr))
sch.label("VCXO_VDD", (vvdd[0] + 1.27, yr))
flag((vvdd[0] + 25.4, yr))
# outputs: FPGA PLL input direct (no R: fastest edge, review MINOR-4); block F's buffer via 33R
node = (vout[0] + 7.62, vout[1])
sch.wire(vout, node, (node[0] + 15.24, node[1]))
d.glabel("VCXO_CLK", (node[0] + 15.24, node[1]), "R", "output")
sch.wire(node, (node[0], node[1] + 10.16))
r, a, b = d.series("33R", (node[0] + 10.16, node[1] + 10.16))
sch.wire((node[0], node[1] + 10.16), a)
sch.wire(b, (node[0] + 22.86, node[1] + 10.16))
d.glabel("MCLK_Q", (node[0] + 22.86, node[1] + 10.16), "R", "output")
T("Tune: 1-bit delta-sigma from ECP5 N4, 2 x (100k, 1u): 1.59 Hz poles,\n> 16 bits below 2 Hz; firmware clamps Vc to 0.3-3.0 V.\n"
  "Fixed-XO fallback on the same land: fit the 0R to VDD, remove the series 0R.", (x0 - 5.08, VY + 20.32))
T("VCXO_CLK -> ECP5 P6 (LLC_GPLL0T_IN), shortest branch, no R.\nMCLK_Q -> block F's SN74LVC2G34 (MCLK_Q).\n"
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
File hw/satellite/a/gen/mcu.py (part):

"""mcu.py -- block E sheet "mcu": RP2350B with the Raspberry Pi reference regulator and decoupling,
W25Q128 boot flash, 12 MHz crystal, BOOTSEL and RUN, USB series resistors, the PIO link and SSPI
configuration pins to the FPGA, ILIM_SEL, IBUS_SENSE and the knob ADCs (references 700-799, A3).

Sources: design/parts/E-mcu-rp2350b.md, E-mcu-passives.md (Raspberry Pi RP2350B Minimal board values),
E-xtal-12mhz.md, E-flash-w25q128.md, E-pinmap.md (net per pin, read by e_pins.py), chips/rp2350.md.
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sch.wire((x - 15.24, YR), a)
sch.wire(b, (x + 5.08, YR))
d.cap_down("4u7", (x + 5.08, YR), decouples=f"{REF}.61")
sch.label("VREG_AVDD", (x + 1.27, YR))
flag((x + 12.7, YR))
sch.wire((x + 5.08, YR), (x + 12.7, YR))
# VREG_VIN: +3V3, CIN 4u7 (0402 small pads, as the reference)
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d.cap_down("4u7", (last + 10.16, YR), decouples=f"{REF}.51")      # second 4u7, DVDD opposite the regulator
last += 10.16
sch.wire((x_fb, YR), (last, YR))
sch.label("DVDD_RP", (x_fb + 1.27, YR))
flag((x_fb, yl))
# IOVDD x8, QSPI_IOVDD, USB_OTP_VDD on +3V3: 10u bulk + 100n per IOVDD; 68/69 share one 100n
io = ["5", "15", "24", "29", "41", "50", "60", "76", "69", "68"]
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        d.cap_down("100n", (xx + 5.08, YR), decouples=f"{REF}.{n}")
sch.wire((x0 - 17.78, YR), (P["69"][0] + 5.08, YR))
sch.wire((P["69"][0] + 5.08, YR), (P["68"][0], YR))
# ADC_AVDD: +3V3 -> 10R -> ADC_AVDD (4u7 + 100n at pin 59); also KNOB_REF's source on the io sheet
x = up_to_rail("59")
d.rail("+3V3", (x - 22.86, YR))
r, a, b = d.series("10R", (x - 15.24, YR))
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T("ABM8-272-T3 12 MHz with 15p + 15p and 1k\nat XOUT: Raspberry Pi's tuned network\n(guide 4); traces < 5 mm.",
  (xc - 22.86, xout[1] + 40.64))
# RUN: 10k pull-up, reset button to GND, to the debug header
run = pin("35")
j = (run[0] - 7.62, run[1])
d.pullup("10k", j, text_left=False)
sch.wire(run, (run[0] - 15.24, run[1]))
sw = sch.symbol("Switch:SW_Push", d.ref("SW"), "RUN", (run[0] - 15.24, run[1] + 5.08), rot=90,
                footprint="Button_Switch_SMD:SW_Push_1P1T_XKB_TS-1187A",
                fields=fields("TS-1187A-B-A-B", "XKB Connection", "C318884"),
                ref_at=(run[0] - 22.86, run[1] + 3.81), value_at=(run[0] - 22.86, run[1] + 6.35), justify="")
d.gnd(sw.pin("2") if sw.pin("2")[1] > sw.pin("1")[1] else sw.pin("1"))
sch.wire((run[0] - 15.24, run[1]), (run[0] - 22.86, run[1]))
d.glabel("RUN", (run[0] - 22.86, run[1]), "L", "bidirectional")
# QSPI flash, pins in the same order as the RP2350's: straight wires
ss = pin("75")
FX = ss[0] + 53.34
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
